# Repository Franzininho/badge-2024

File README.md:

# Franzininho Badge 2024  
  
Este é um projeto de badge/crachá eletrônico para eventos, envisionado pelo pessoal da comunidade Franzininho.
  
## Hardware
  
- MCU: WCH CH32V003F4P6
- Displays: E-paper modules da WeAct Studio (SPI) e Modulo OLED (I2C)
- Bateria: CR2032
- Botões: ON, RESET e USER
- Pinos de UART, I2C e SPI disponíveis para permitir hacks/expansões do projeto
  
## Imagens

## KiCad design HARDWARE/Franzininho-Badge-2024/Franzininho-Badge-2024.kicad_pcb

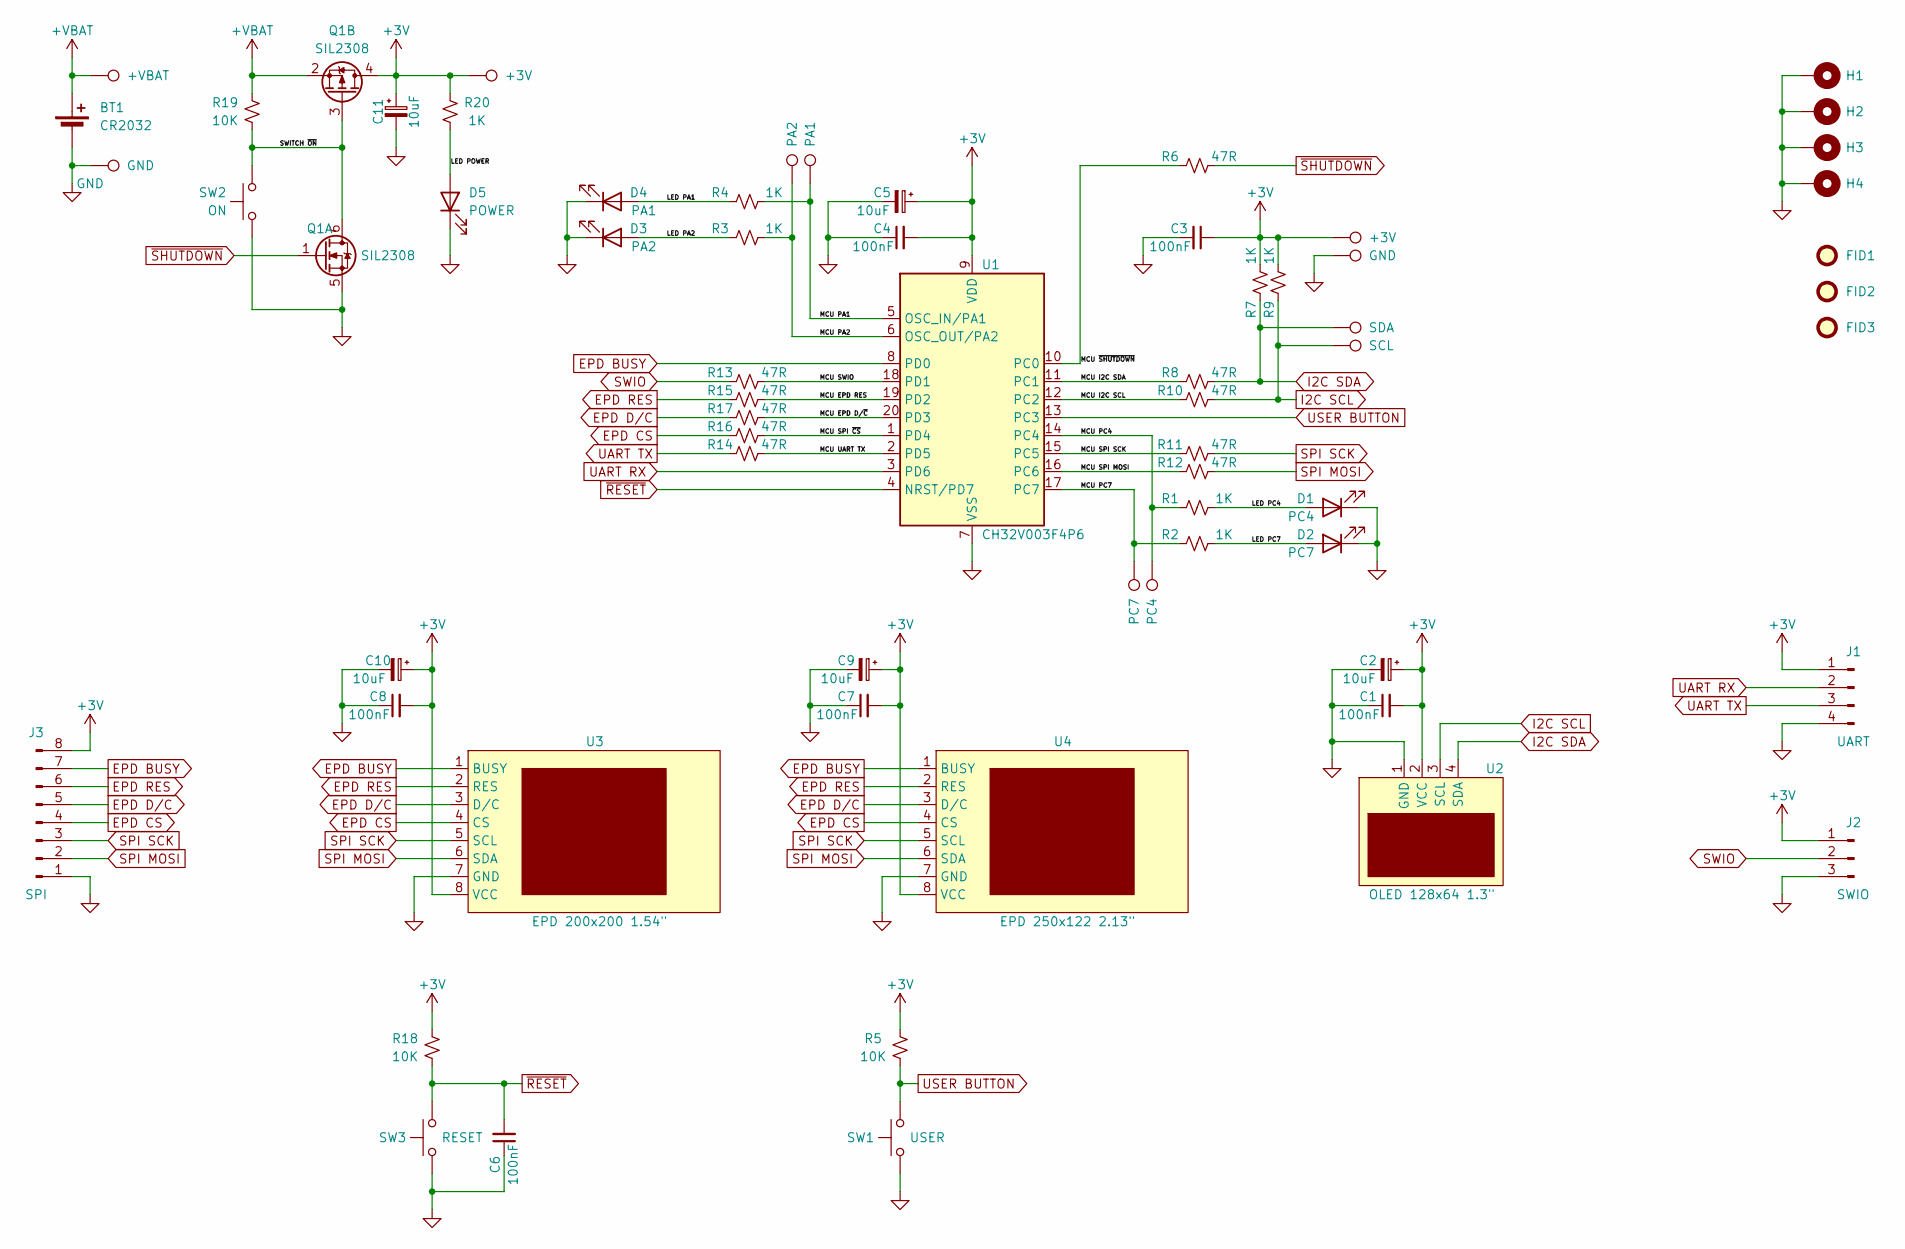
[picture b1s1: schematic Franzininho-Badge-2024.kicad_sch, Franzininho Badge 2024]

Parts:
BT1: CR2032; BatteryHolder_Keystone_3002_1x2032
C1, C3, C4, C6, C7, C8: 100nF; C_0603_1608Metric_Pad1.08x0.95mm_HandSolder
C2, C5, C9, C10, C11: 10uF; C_0805_2012Metric_Pad1.18x1.45mm_HandSolder
D1: PC4; LED_0603_1608Metric_Pad1.05x0.95mm_HandSolder
D2: PC7; LED_0603_1608Metric_Pad1.05x0.95mm_HandSolder
D3: PA2; LED_0603_1608Metric_Pad1.05x0.95mm_HandSolder
D4: PA1; LED_0603_1608Metric_Pad1.05x0.95mm_HandSolder
D5: POWER; LED_0603_1608Metric_Pad1.05x0.95mm_HandSolder
FID1, FID2, FID3: Fiducial; Fiducial_0.75mm_Mask1.5mm
H1, H2, H3, H4: MountingHole_Pad; MountingHole_3.2mm_M3_Pad
J1: UART; PinHeader_1x04_P2.54mm_Horizontal
J2: SWIO; PinHeader_1x03_P2.54mm_Horizontal
J3: SPI; PinHeader_1x08_P2.54mm_Horizontal
Q1: SIL2308; SOT-23-6_Handsoldering
R1, R2, R3, R4, R7, R9, R20: 1K; R_0603_1608Metric_Pad0.98x0.95mm_HandSolder
R5, R18, R19: 10K; R_0603_1608Metric_Pad0.98x0.95mm_HandSolder
R6, R8, R10, R11, R12, R13, R14, R15, R16, R17: 47R; R_0603_1608Metric_Pad0.98x0.95mm_HandSolder
SW1: USER; SW_Push_1P1T_NO_CK_KSC6xxJ
SW2: ON; SW_Push_1P1T_NO_CK_KSC6xxJ
SW3: RESET; SW_Push_1P1T_NO_CK_KSC6xxJ
TP1: SDA; TestPoint_THTPad_D1.5mm_Drill0.7mm
TP2: SCL; TestPoint_THTPad_D1.5mm_Drill0.7mm
TP3, TP11: +3V; TestPoint_THTPad_D1.5mm_Drill0.7mm
TP4, TP9: GND; TestPoint_THTPad_D1.5mm_Drill0.7mm
TP5: PC4; TestPoint_THTPad_D1.5mm_Drill0.7mm
TP6: PC7; TestPoint_THTPad_D1.5mm_Drill0.7mm
TP7: PA2; TestPoint_THTPad_D1.5mm_Drill0.7mm
TP8: PA1; TestPoint_THTPad_D1.5mm_Drill0.7mm
TP10: +VBAT; TestPoint_THTPad_D1.5mm_Drill0.7mm
U1: CH32V003F4P6; TSSOP-20_4.4x6.5mm_P0.65mm
U2: OLED 128x64 1.3"; OLED 128x64 1.3in
U3: EPD 200x200 1.54"; EPAPER_1.54in_200x200
U4: EPD 250x122 2.13"; EPAPER_2.13in_250x122

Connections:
+3V: C1.2, C2.1, C3.1, C4.2, C5.1, C7.2, C8.2, C9.1, C10.1, C11.1, J1.1, J2.1, J3.8, Q1.4 (D2), R5.2, R7.2, R9.2, R18.2, R20.2, TP3.1, TP11.1, U1.9 (VDD), U2.2 (VCC), U3.8 (VCC), U4.8 (VCC)
+VBAT: BT1.1 (+), Q1.2 (S2), R19.2, TP10.1
/LED PA1: D4.2 (A), R4.1
/LED PA2: D3.2 (A), R3.1
/LED PC4: D1.2 (A), R1.2
/LED PC7: D2.2 (A), R2.2
/LED POWER: D5.2 (A), R20.1
/MCU EPD RES: R15.2, U1.19 (PD2)
/MCU EPD D/~C: R17.2, U1.20 (PD3)
/MCU I2C SCL: R10.1, U1.12 (PC2)
/MCU I2C SDA: R8.1, U1.11 (PC1)
/MCU PA1: R4.2, TP8.1, U1.5 (OSC_IN/PA1)
/MCU PA2: R3.2, TP7.1, U1.6 (OSC_OUT/PA2)
/MCU PC4: R1.1, TP5.1, U1.14 (PC4)
/MCU PC7: R2.1, TP6.1, U1.17 (PC7)
/MCU SPI MOSI: R12.1, U1.16 (PC6)
/MCU SPI SCK: R11.1, U1.15 (PC5)
/MCU SPI ~CS: R16.2, U1.1 (PD4)
/MCU SWIO: R13.2, U1.18 (PD1)
/MCU UART TX: R14.2, U1.2 (PD5)
/MCU ~SHUTDOWN: R6.1, U1.10 (PC0)
/SWITCH ~ON: Q1.3 (G2), Q1.6 (D1), R19.1, SW2.2
EPD BUSY: J3.7, U1.8 (PD0), U3.1 (BUSY), U4.1 (BUSY)
EPD CS: J3.4, R16.1, U3.4 (CS), U4.4 (CS)
EPD D/C: J3.5, R17.1, U3.3 (D/C), U4.3 (D/C)
EPD RES: J3.6, R15.1, U3.2 (RES), U4.2 (RES)
GND: BT1.2 (-), C1.1, C2.2, C3.2, C4.1, C5.2, C6.1, C7.1, C8.1, C9.2, C10.2, C11.2, D1.1 (K), D2.1 (K), D3.1 (K), D4.1 (K), D5.1 (K), H1.1, H2.1, H3.1, H4.1, J1.4, J2.3, J3.1, Q1.5 (S1), SW1.1, SW2.1, SW3.1, TP4.1, TP9.1, U1.7 (VSS), U2.1 (GND), U3.7 (GND), U4.7 (GND)
I2C SCL: R9.1, R10.2, TP2.1, U2.3 (SCL)
I2C SDA: R7.1, R8.2, TP1.1, U2.4 (SDA)
SPI MOSI: J3.2, R12.2, U3.6 (SDA), U4.6 (SDA)
SPI SCK: J3.3, R11.2, U3.5 (SCL), U4.5 (SCL)
SWIO: J2.2, R13.1
UART RX: J1.2, U1.3 (PD6)
UART TX: J1.3, R14.1
USER BUTTON: R5.1, SW1.2, U1.13 (PC3)
~RESET: C6.2, R18.1, SW3.2, U1.4 (NRST/PD7)
~SHUTDOWN: Q1.1 (G1), R6.2

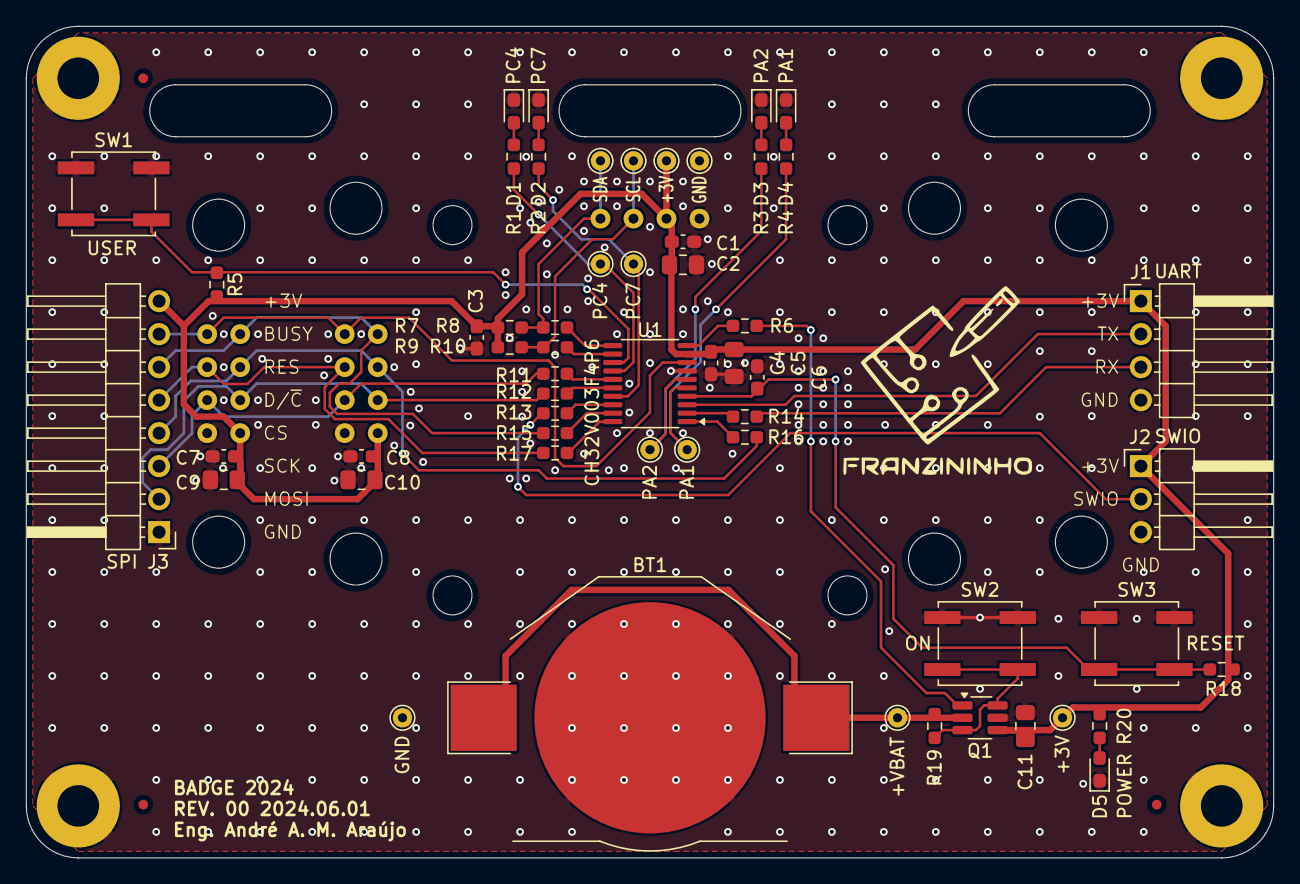
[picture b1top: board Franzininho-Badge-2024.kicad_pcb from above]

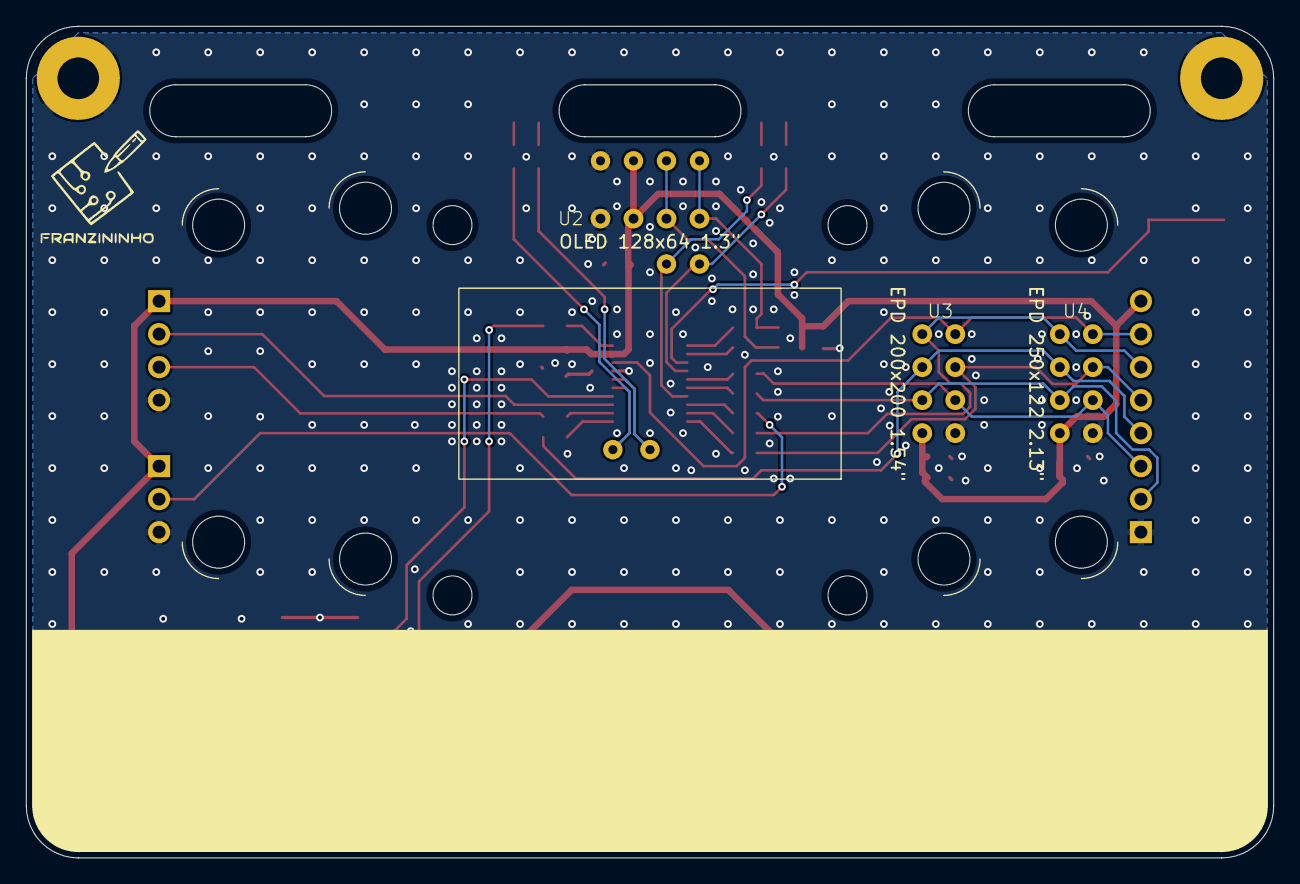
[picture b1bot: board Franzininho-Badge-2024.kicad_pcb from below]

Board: 2 copper layers, 96.0 x 64.0 mm, 66 parts (3 on the bottom side), 37 nets.

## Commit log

2024-03-26 Criação do projeto no KiCad.
2024-05-21 Adicionando displays.
2024-05-21 Esboço inicial do layout.
2024-05-25 Adicionado display de 2.13in; continuação do layout.
2024-05-26 Adicionado circuito liga-desliga; finalizando layout.
2024-05-31 Finalização do projeto; adicionados test points e LEDs; adicionado conector para SPI; ajuste nas marcações; renumeração; ajustes no layout.
2024-05-31 Enviando para revisão pela comunidade.
2024-06-01 Finalização do esquemático e layout.
2024-06-01 Adicionadas imagens da PCB (renders).
2024-06-01 Adicionados arquivos de fabricação.
2024-06-01 Revisão de valores dos resistores. Geração de novo PDF do esquemático.
2024-06-01 Gerados arquivos de fabricação com Plugin JLCPCB. Projeto finalizado e compradas 10 placas de protótipo na JLCPCB.
